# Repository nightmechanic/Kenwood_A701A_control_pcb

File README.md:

Kenwood_A701A_control_pcb
=========================

This is a Control PCB for a Kenwood A701A kitchen mixer.

Created for our kitchen mixer restoration project.

Benefits:
  - Allows using a common 470 ohm 25W cement resistor (+ a 2W 10kohm ) instead of the expensive DR type resistor originaly used by Kenwood.
  - Uses terminal blocks for wire connections
  - the components are mounted on the PCB instead of floating around...

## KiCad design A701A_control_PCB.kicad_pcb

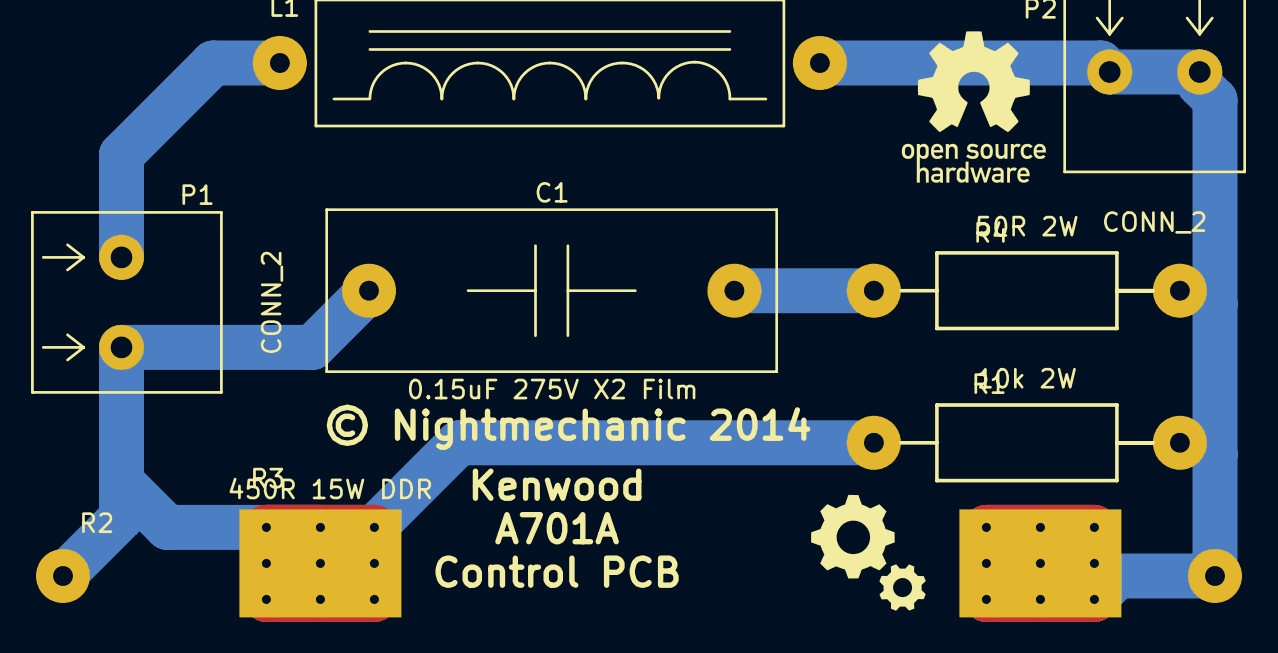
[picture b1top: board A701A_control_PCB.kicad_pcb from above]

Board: 2 copper layers, 10 parts (0 on the bottom side), 4 nets.

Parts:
C1: 0.15uF 275V X2 Film; KEMET_PME271M615K
L1: 22uH 3A choke; EPCOS_B82111EC22
P1, P2: CONN_2; PHOENIX_TERMINAL_PTS1.5_2-5.0-H
R1: 10k 2W; VISHAY_PR02
R2: 470R 25W; XICON_CR25
R3: 450R 15W DDR; DDR_15W
R4: 50R 2W; VISHAY_PR02
VAL: REF; Gears_F.SilkS_8mm
VAL#2: REF; OSHW_F.SilkS_8mm

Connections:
unnamed: C1.1, P1.2, R1.1, R2.1, R3.1
unnamed: C1.2, R4.1
unnamed: L1.1, P1.1
unnamed: L1.2, P2.1, P2.2, R1.2, R2.2, R3.2, R4.2

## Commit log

2014-05-28 First revision
    Layout almost done (missing board edge
2014-05-30 Layout done
2015-12-06 Update README.md
    Typo...

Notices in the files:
A701A_control_PCB.kicad_pcb:
© Nightmechanic 2014
